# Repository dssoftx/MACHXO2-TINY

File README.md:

# MACHXO2-MINI

Minimal FPGA board built around a Lattice MachXO2-4000HC (TQFP-144), designed by DsSoft.

## Specs
- **FPGA:** LCMXO2-4000HC-4TG144C, with 4320 LUTs and on-chip configuration flash
- **Power:** USB-C (power only) feeds an AP2112K-3.3 regulator. Everything runs from a single 3.3 V rail.
- **Clock:** 12 MHz oscillator on pin 128 (PCLKT0_1)
- **I/O:** 4 LEDs, 1 user button, a UART header, and 72 GPIO on two 2×20 headers
- **PCB:** 4 layers (signal / GND / 3V3 / signal)

## Pinout
| Signal | FPGA pin |
|---|---|
| CLK12 | 128 |
| LED0–3 | 97, 98, 99, 100 |
| BTN0 (active-low, enable the internal pull-up) | 96 |
| UART TX / RX | 111 / 112 |

The GPIO header mapping is listed in `rtl/blinky.lpf`. Header pins 1–2 are 3V3 and pins 39–40 are GND.

**J2 JTAG:** 1 = VREF, 2 = TCK, 3 = TDI, 4 = TDO, 5 = TMS, 6 = GND
**J3 UART:** 1 = TX, 2 = RX, 3 = GND

## Programming
Wire any FT2232H board to J2, then:
```
openFPGALoader --detect
openFPGALoader -c ft2232 -f blinky.jed   # write to internal flash
```
Build bitstreams in Lattice Diamond, starting from `rtl/blinky.v` and `rtl/blinky.lpf`.

## Bring-up
1. Inspect the TQFP pins for solder bridges (ideally assemble with JLC, BOM Coming)
2. Measure 3V3 to GND. It must not read as a short.
3. Plug in USB. The PWR LED should light and C17 should read 3.3 V.
4. Run `openFPGALoader --detect` and check that the FPGA is found.
5. Flash the blinky.

## Key parts
| Ref | Part | LCSC |
|---|---|---|
| U1 | LCMXO2-4000HC-4TG144C | C1521625 |
| U2 | AP2112K-3.3TRG1 (Diodes) | C51118 |
| X1 | ASE-12.000MHZ-LC-T (Abracon) | C596950 |
| J1 | HRO TYPE-C-31-M-12 | — |

## Files
- `machxo2-mini.kicad_sch`: the schematic
- `rtl/`: blinky design and its constraints file
- `gen_schematic.py`: the script that generates the schematic

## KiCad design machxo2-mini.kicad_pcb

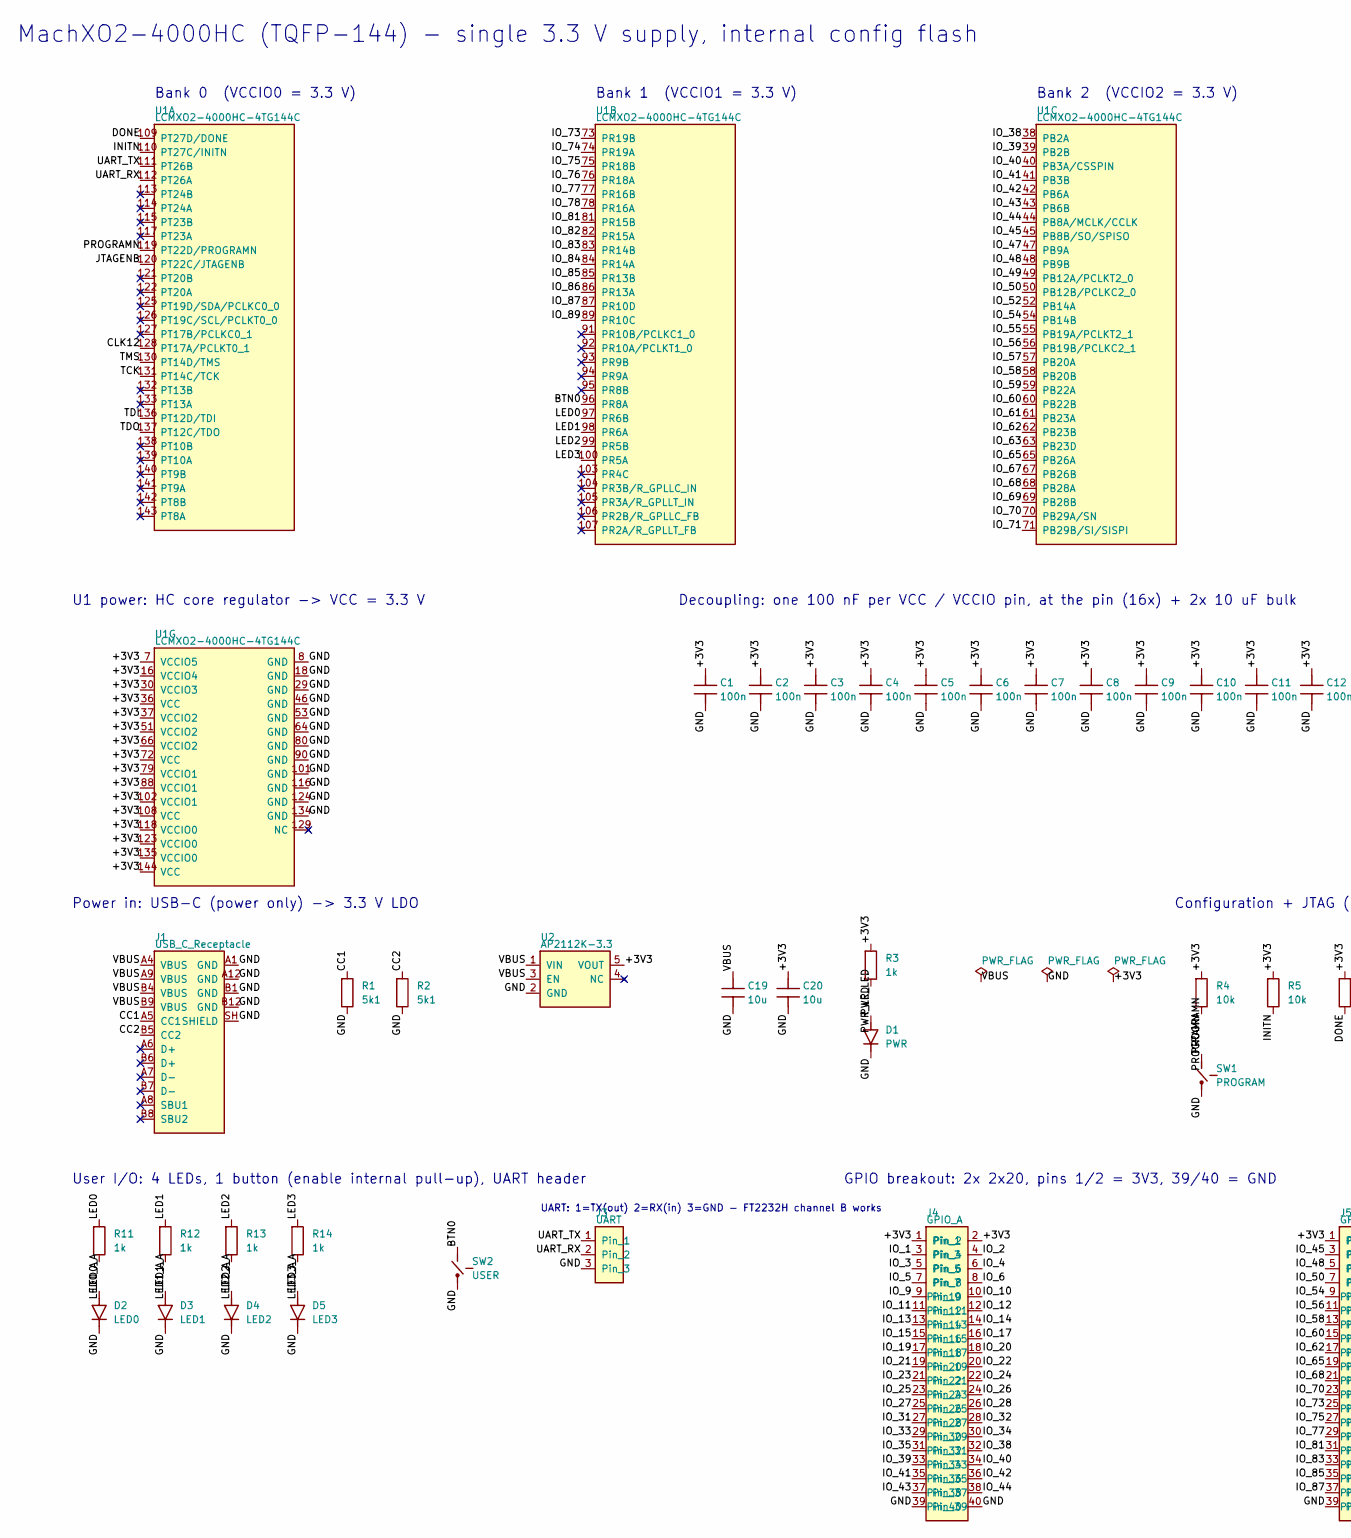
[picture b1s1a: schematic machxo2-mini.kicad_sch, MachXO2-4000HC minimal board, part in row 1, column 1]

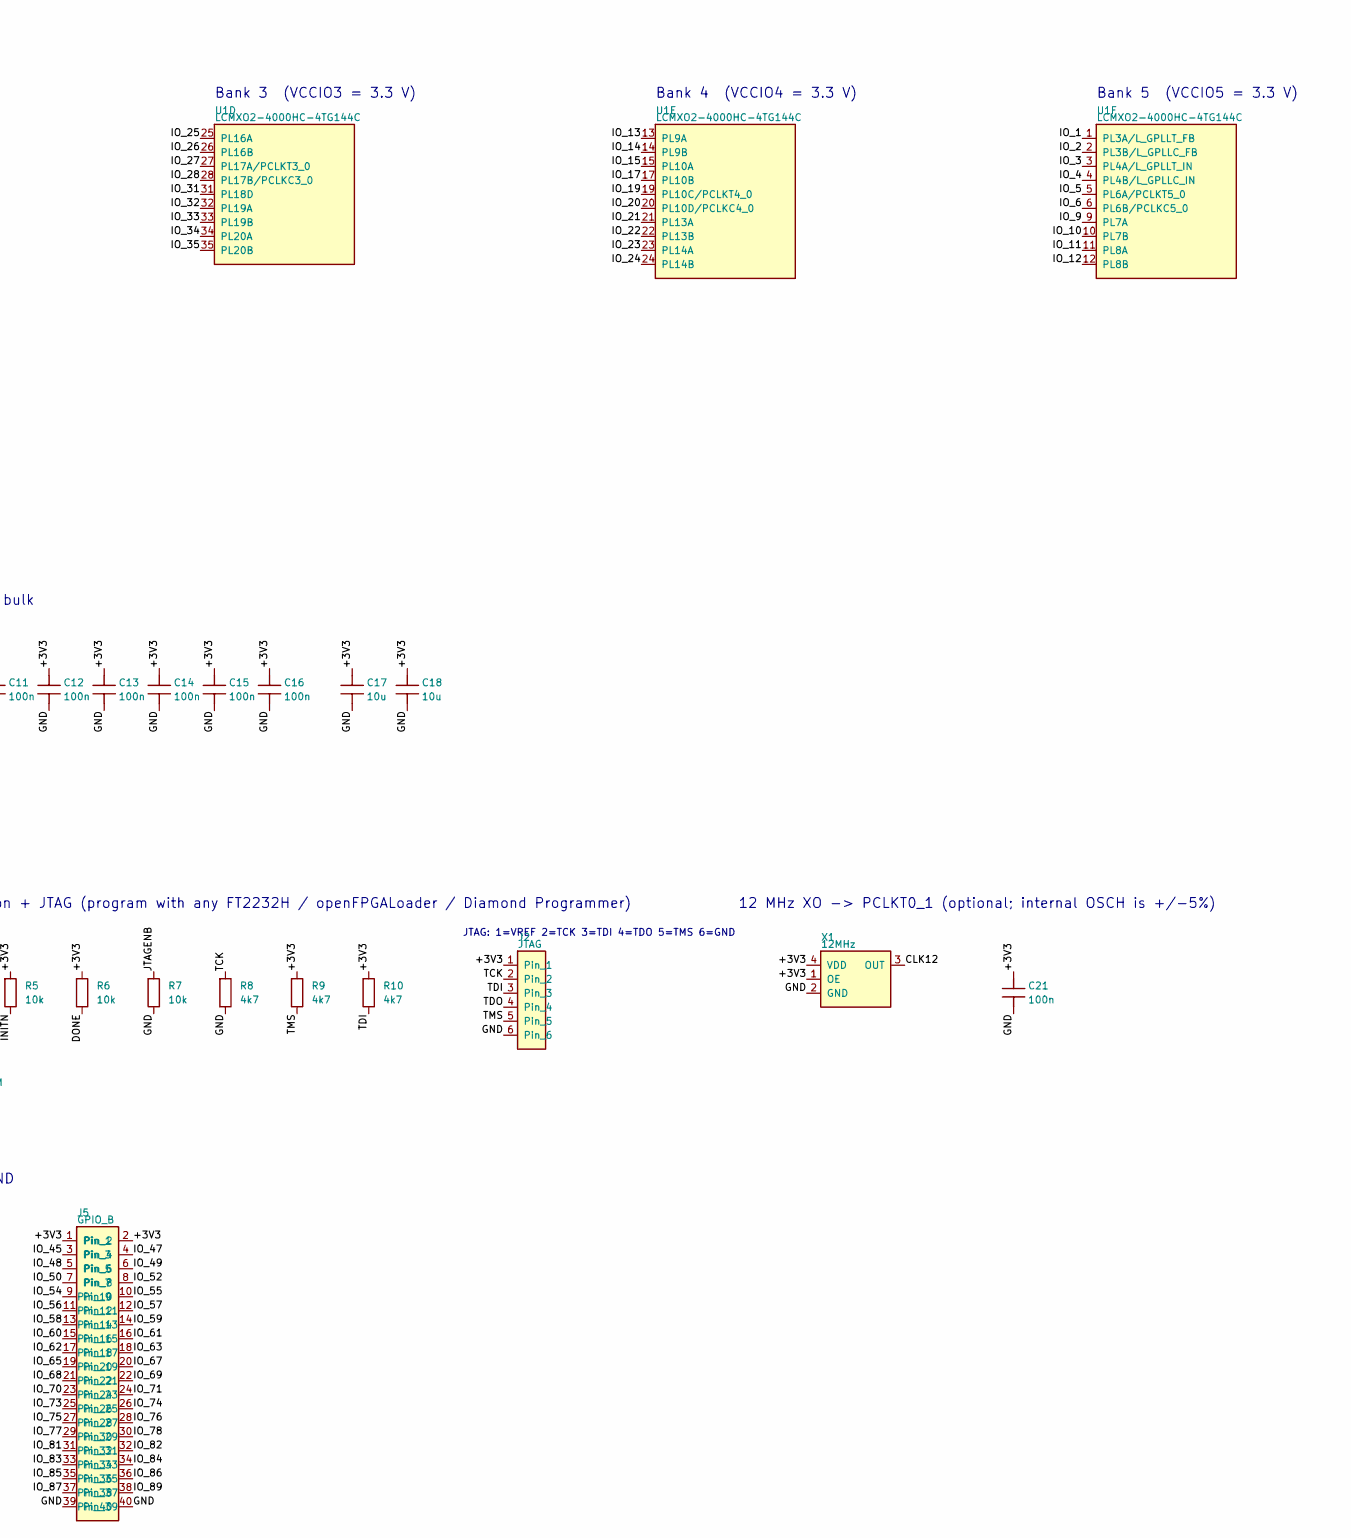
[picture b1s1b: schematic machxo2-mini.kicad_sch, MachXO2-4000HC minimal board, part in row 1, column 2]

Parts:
C1, C2, C3, C4, C5, C6, C7, C8, C9, C10, C11, C12, C13, C14, C15, C16, C21: 100n; C_0603_1608Metric
C17, C18, C19, C20: 10u; C_0805_2012Metric
D1: PWR; LED_0603_1608Metric
D2: LED0; LED_0603_1608Metric
D3: LED1; LED_0603_1608Metric
D4: LED2; LED_0603_1608Metric
D5: LED3; LED_0603_1608Metric
J1: USB_C_Receptacle; USB_C_Receptacle_HRO_TYPE-C-31-M-12
J2: JTAG; PinHeader_1x06_P2.54mm_Vertical
J3: UART; PinHeader_1x03_P2.54mm_Vertical
J4: GPIO_A; PinHeader_2x20_P2.54mm_Vertical
J5: GPIO_B; PinHeader_2x20_P2.54mm_Vertical
R1, R2: 5k1; R_0603_1608Metric
R3, R11, R12, R13, R14: 1k; R_0603_1608Metric
R4, R5, R6, R7: 10k; R_0603_1608Metric
R8, R9, R10: 4k7; R_0603_1608Metric
SW1: PROGRAM; SW_SPST_TL3342
SW2: USER; SW_SPST_TL3342
U1: LCMXO2-4000HC-4TG144C; TQFP-144_20x20mm_P0.5mm
U2: AP2112K-3.3; SOT-23-5
X1: 12MHz; Oscillator_SMD_Abracon_ASE-4Pin_3.2x2.5mm

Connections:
/+3V3: C1.1, C2.1, C3.1, C4.1, C5.1, C6.1, C7.1, C8.1, C9.1, C10.1, C11.1, C12.1, C13.1, C14.1, C15.1, C16.1, C17.1, C18.1, C20.1, C21.1, J2.1, J4.1, J4.2, J5.1, J5.2, R3.1, R4.1, R5.1, R6.1, R9.1, R10.1, U1.7 (VCCIO5), U1.16 (VCCIO4), U1.30 (VCCIO3), U1.36 (VCC), U1.37 (VCCIO2), U1.51 (VCCIO2), U1.66 (VCCIO2), U1.72 (VCC), U1.79 (VCCIO1), U1.88 (VCCIO1), U1.102 (VCCIO1), U1.108 (VCC), U1.118 (VCCIO0), U1.123 (VCCIO0), U1.135 (VCCIO0), U1.144 (VCC), U2.5 (VOUT), X1.1 (OE), X1.4 (VDD)
/BTN0: SW2.1, U1.96 (PR8A)
/CC1: J1.A5 (CC1), R1.1
/CC2: J1.B5 (CC2), R2.1
/CLK12: U1.128 (PT17A/PCLKT0_1), X1.3 (OUT)
/DONE: R6.2, U1.109 (PT27D/DONE)
/GND: C1.2, C2.2, C3.2, C4.2, C5.2, C6.2, C7.2, C8.2, C9.2, C10.2, C11.2, C12.2, C13.2, C14.2, C15.2, C16.2, C17.2, C18.2, C19.2, C20.2, C21.2, D1.1 (K), D2.1 (K), D3.1 (K), D4.1 (K), D5.1 (K), J1.A1 (GND), J1.A12 (GND), J1.B1 (GND), J1.B12 (GND), J1.SH (SHIELD), J2.6, J3.3, J4.39, J4.40, J5.39, J5.40, R1.2, R2.2, R7.2, R8.2, SW1.2, SW2.2, U1.8 (GND), U1.18 (GND), U1.29 (GND), U1.46 (GND), U1.53 (GND), U1.64 (GND), U1.80 (GND), U1.90 (GND), U1.101 (GND), U1.116 (GND), U1.124 (GND), U1.134 (GND), U2.2 (GND), X1.2 (GND)
/INITN: R5.2, U1.110 (PT27C/INITN)
/IO_1: J4.3, U1.1 (PL3A/L_GPLLT_FB)
/IO_2: J4.4, U1.2 (PL3B/L_GPLLC_FB)
/IO_3: J4.5, U1.3 (PL4A/L_GPLLT_IN)
/IO_4: J4.6, U1.4 (PL4B/L_GPLLC_IN)
/IO_5: J4.7, U1.5 (PL6A/PCLKT5_0)
/IO_6: J4.8, U1.6 (PL6B/PCLKC5_0)
/IO_9: J4.9, U1.9 (PL7A)
/IO_10: J4.10, U1.10 (PL7B)
/IO_11: J4.11, U1.11 (PL8A)
/IO_12: J4.12, U1.12 (PL8B)
/IO_13: J4.13, U1.13 (PL9A)
/IO_14: J4.14, U1.14 (PL9B)
/IO_15: J4.15, U1.15 (PL10A)
/IO_17: J4.16, U1.17 (PL10B)
/IO_19: J4.17, U1.19 (PL10C/PCLKT4_0)
/IO_20: J4.18, U1.20 (PL10D/PCLKC4_0)
/IO_21: J4.19, U1.21 (PL13A)
/IO_22: J4.20, U1.22 (PL13B)
/IO_23: J4.21, U1.23 (PL14A)
/IO_24: J4.22, U1.24 (PL14B)
/IO_25: J4.23, U1.25 (PL16A)
/IO_26: J4.24, U1.26 (PL16B)
/IO_27: J4.25, U1.27 (PL17A/PCLKT3_0)
/IO_28: J4.26, U1.28 (PL17B/PCLKC3_0)
/IO_31: J4.27, U1.31 (PL18D)
/IO_32: J4.28, U1.32 (PL19A)
/IO_33: J4.29, U1.33 (PL19B)
/IO_34: J4.30, U1.34 (PL20A)
/IO_35: J4.31, U1.35 (PL20B)
/IO_38: J4.32, U1.38 (PB2A)
/IO_39: J4.33, U1.39 (PB2B)
/IO_40: J4.34, U1.40 (PB3A/CSSPIN)
/IO_41: J4.35, U1.41 (PB3B)
/IO_42: J4.36, U1.42 (PB6A)
/IO_43: J4.37, U1.43 (PB6B)
/IO_44: J4.38, U1.44 (PB8A/MCLK/CCLK)
/IO_45: J5.3, U1.45 (PB8B/SO/SPISO)
/IO_47: J5.4, U1.47 (PB9A)
/IO_48: J5.5, U1.48 (PB9B)
/IO_49: J5.6, U1.49 (PB12A/PCLKT2_0)
/IO_50: J5.7, U1.50 (PB12B/PCLKC2_0)
/IO_52: J5.8, U1.52 (PB14A)
/IO_54: J5.9, U1.54 (PB14B)
/IO_55: J5.10, U1.55 (PB19A/PCLKT2_1)
/IO_56: J5.11, U1.56 (PB19B/PCLKC2_1)
/IO_57: J5.12, U1.57 (PB20A)
/IO_58: J5.13, U1.58 (PB20B)
/IO_59: J5.14, U1.59 (PB22A)
/IO_60: J5.15, U1.60 (PB22B)
/IO_61: J5.16, U1.61 (PB23A)
/IO_62: J5.17, U1.62 (PB23B)
/IO_63: J5.18, U1.63 (PB23D)
/IO_65: J5.19, U1.65 (PB26A)
/IO_67: J5.20, U1.67 (PB26B)
/IO_68: J5.21, U1.68 (PB28A)
/IO_69: J5.22, U1.69 (PB28B)
/IO_70: J5.23, U1.70 (PB29A/SN)
/IO_71: J5.24, U1.71 (PB29B/SI/SISPI)
/IO_73: J5.25, U1.73 (PR19B)
/IO_74: J5.26, U1.74 (PR19A)
/IO_75: J5.27, U1.75 (PR18B)
/IO_76: J5.28, U1.76 (PR18A)
/IO_77: J5.29, U1.77 (PR16B)
/IO_78: J5.30, U1.78 (PR16A)
/IO_81: J5.31, U1.81 (PR15B)
/IO_82: J5.32, U1.82 (PR15A)
/IO_83: J5.33, U1.83 (PR14B)
/IO_84: J5.34, U1.84 (PR14A)
/IO_85: J5.35, U1.85 (PR13B)
/IO_86: J5.36, U1.86 (PR13A)
/IO_87: J5.37, U1.87 (PR10D)
/IO_89: J5.38, U1.89 (PR10C)
/JTAGENB: R7.1, U1.120 (PT22C/JTAGENB)
/LED0: R11.1, U1.97 (PR6B)
/LED0_A: D2.2 (A), R11.2
/LED1: R12.1, U1.98 (PR6A)
/LED1_A: D3.2 (A), R12.2
/LED2: R13.1, U1.99 (PR5B)
/LED2_A: D4.2 (A), R13.2
/LED3: R14.1, U1.100 (PR5A)
/LED3_A: D5.2 (A), R14.2
/PROGRAMN: R4.2, SW1.1, U1.119 (PT22D/PROGRAMN)
/PWR_LED: D1.2 (A), R3.2
/TCK: J2.2, R8.1, U1.131 (PT14C/TCK)
/TDI: J2.3, R10.2, U1.136 (PT12D/TDI)
/TDO: J2.4, U1.137 (PT12C/TDO)
/TMS: J2.5, R9.2, U1.130 (PT14D/TMS)
/UART_RX: J3.2, U1.112 (PT26A)
/UART_TX: J3.1, U1.111 (PT26B)
/VBUS: C19.1, J1.A4 (VBUS), J1.A9 (VBUS), J1.B4 (VBUS), J1.B9 (VBUS), U2.1 (VIN), U2.3 (EN)

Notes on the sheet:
MachXO2-4000HC (TQFP-144) - single 3.3 V supply, internal config flash
Bank 0 (VCCIO0 = 3.3 V)
Bank 1 (VCCIO1 = 3.3 V)
Bank 2 (VCCIO2 = 3.3 V)
Bank 3 (VCCIO3 = 3.3 V)
Bank 4 (VCCIO4 = 3.3 V)
Bank 5 (VCCIO5 = 3.3 V)
U1 power: HC core regulator -> VCC = 3.3 V
Decoupling: one 100 nF per VCC / VCCIO pin, at the pin (16x) + 2x 10 uF bulk
Power in: USB-C (power only) -> 3.3 V LDO
Configuration + JTAG (program with any FT2232H / openFPGALoader / Diamond Programmer)
JTAG: 1=VREF 2=TCK 3=TDI 4=TDO 5=TMS 6=GND
12 MHz XO -> PCLKT0_1 (optional; internal OSCH is +/-5%)
User I/O: 4 LEDs, 1 button (enable internal pull-up), UART header
UART: 1=TX(out) 2=RX(in) 3=GND - FT2232H channel B works
GPIO breakout: 2x 2x20, pins 1/2 = 3V3, 39/40 = GND

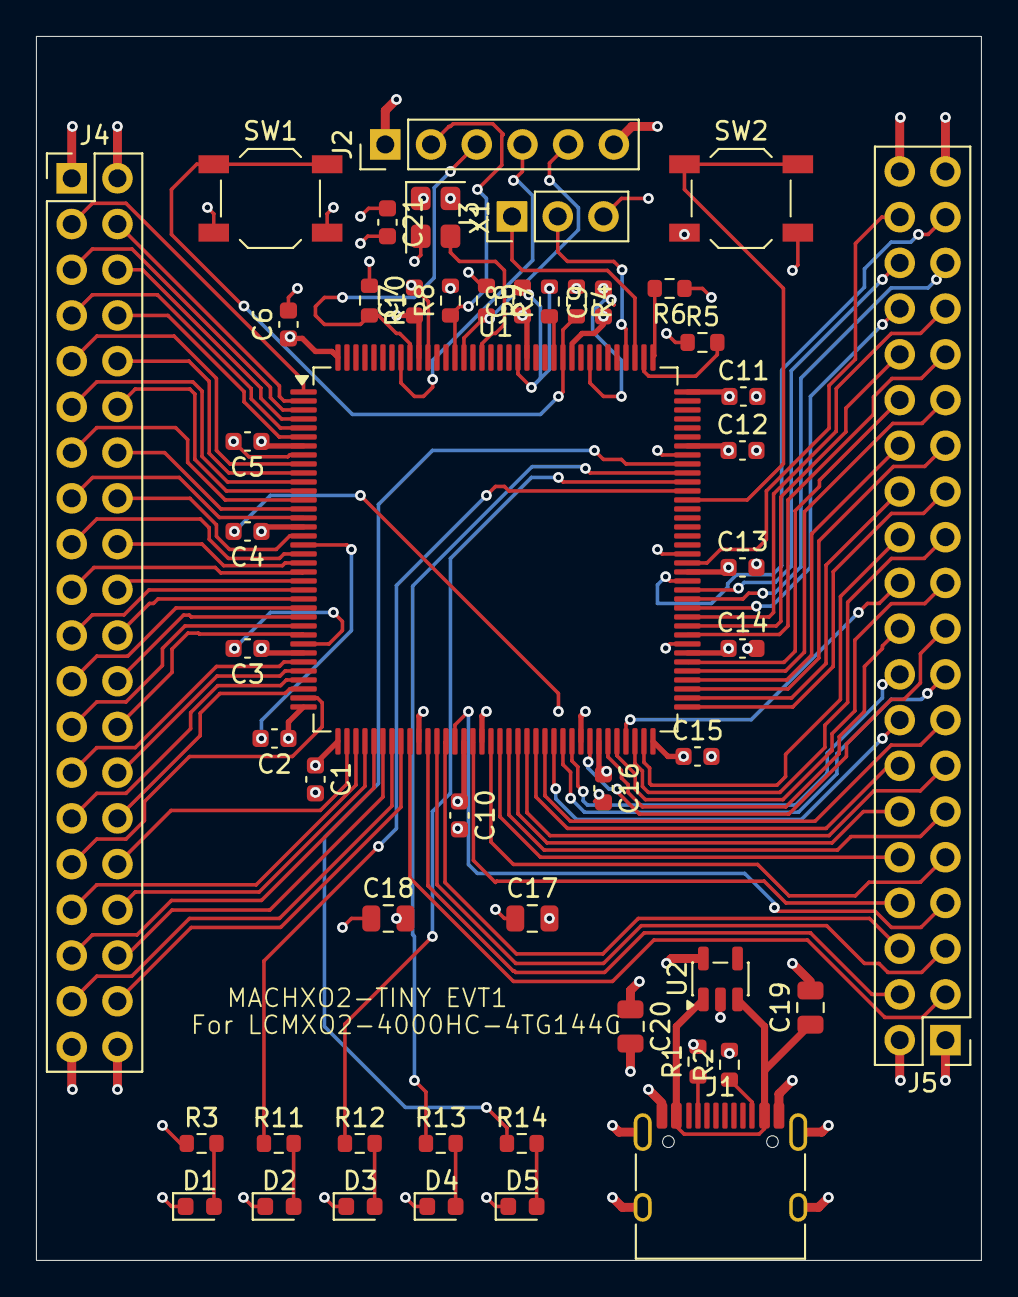
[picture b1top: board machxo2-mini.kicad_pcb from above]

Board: 4 copper layers, 52.5 x 68.0 mm, 50 parts (0 on the bottom side), 98 nets.

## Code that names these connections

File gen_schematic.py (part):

#!/usr/bin/env python3
"""Generate a minimal LCMXO2-4000HC-TG144 board schematic for KiCad 8.

Connectivity is done with local net labels placed on pin endpoints, so the
schematic is purely label-wired (no wires) -- valid and netlists correctly.
"""
import json, sys, uuid
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# --- Clock ------------------------------------------------------------
text('12 MHz XO -> PCLKT0_1 (optional; internal OSCH is +/-5%)', 380, 245, 1.8)
place('XO_4pin', 'X', 395, 255, '12MHz', 'Oscillator:Oscillator_SMD_Abracon_ASE-4Pin_3.2x2.5mm',
      OSC_PINS, {'4': '+3V3', '1': '+3V3', '2': 'GND', '3': 'CLK12'})
passive('C', 430, 260, '100n', '+3V3', 'GND', FP_C)

# --- User I/O ---------------------------------------------------------
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# fix: LED anode should be driven by the resistor; nets above go FPGA->R->LED(A)->K->GND
passive('SW', 100, 310, 'USER', 'BTN0', 'GND', 'Button_Switch_SMD:SW_SPST_TL3342')
place('Conn_01x03', 'J', 125, 305, 'UART', 'Connector_PinHeader_2.54mm:PinHeader_1x03_P2.54mm_Vertical',
      J3_PINS, {'1': 'UART_TX', '2': 'UART_RX', '3': 'GND'})
text('UART: 1=TX(out) 2=RX(in) 3=GND - FT2232H channel B works', 115, 300, 1.27)

# --- GPIO headers -----------------------------------------------------
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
